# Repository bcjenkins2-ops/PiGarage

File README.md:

# PiGarage

Open-source Raspberry Pi power management and audio HAT for automotive head-unit use.

## Features

- **5V 5A Buck Converter** (TPS54560BQDDARQ1) — 7-16V input, Pi 5 compatible
- **I2S DAC** (PCM5122PWR) — 112dB SNR, noise-free audio output to external amplifier
- **ADC** (ADS1115) — 16-bit, for steering wheel resistor ladder controls
- **4-Channel Optoisolated 12V Sensing** — ACC, REV, ILL, AUX via LTV-847S
- **Safe Shutdown** — ACC-triggered power latch with GPIO hold (BCM25), crank ride-through
- **Battery Protection** — UVLO hard cutoff at 12.08V via TL431A comparator
- **Compatible** — Raspberry Pi 3, 4, and 5

## Board

| Parameter | Value |
|-----------|-------|
| Input Voltage | 7-16V (automotive 12V) |
| Output Voltage | 5.0V |
| Output Current | 5A continuous |
| DAC SNR | 112dB |
| DAC Interface | I2S |
| ADC Resolution | 16-bit, 4-channel |
| Sense Inputs | 4ch optoisolated |
| Board Format | Raspberry Pi HAT (65mm x 56.5mm) |

## Directory Layout

```
PiGarage/
├── Hardware/           KiCad 10 schematic, PCB, and custom libraries
├── Production/         Gerbers, drill files, pick-and-place
├── BOM/                Bill of Materials and design notes
├── Images/             Board renders and schematic exports
├── Software/           Power latch daemon and systemd service
└── Docs/               Ordering and assembly guide
```

## Getting Started

See [Docs/ordering-guide.md](Docs/ordering-guide.md) for full instructions on ordering from JLCPCB and assembling the board.

## License

Hardware: [CERN-OHL-S-2.0](https://ohwr.org/cern_ohl_s_v2.txt) — Software: MIT

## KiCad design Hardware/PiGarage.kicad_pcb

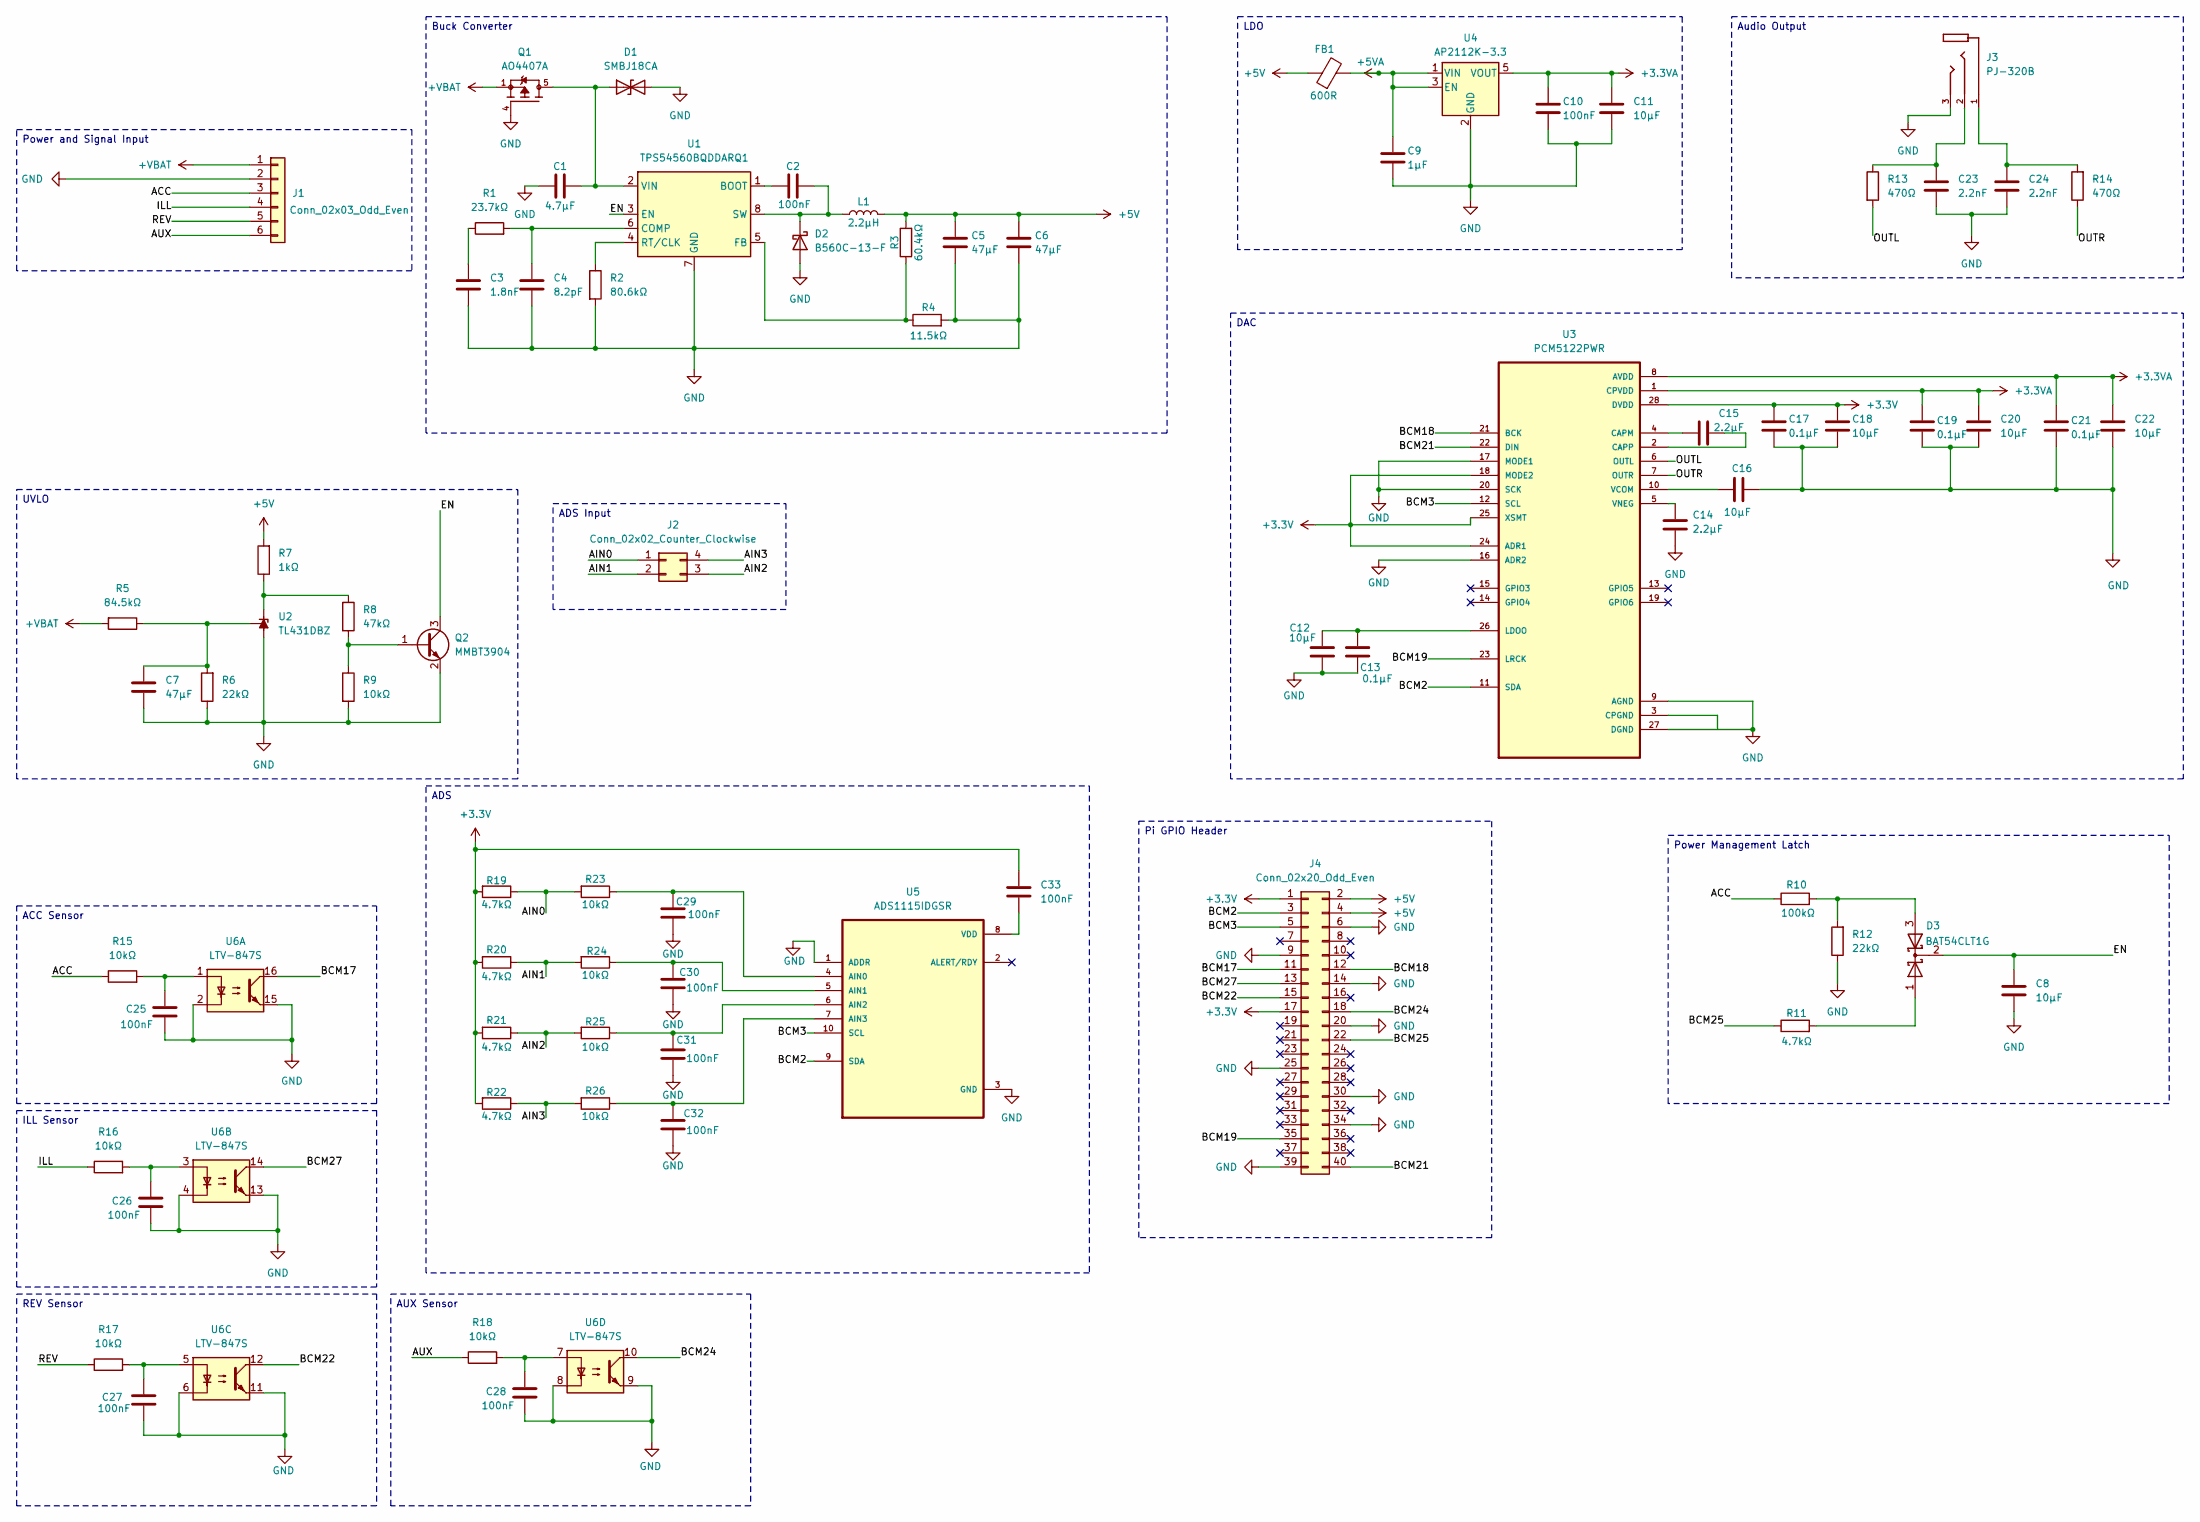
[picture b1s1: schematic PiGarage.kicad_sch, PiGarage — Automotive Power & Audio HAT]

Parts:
C1: 4.7µF; C_1206_3216Metric
C2, C10, C25, C26, C27, C28, C29, C30, C31, C32, C33: 100nF; C_0603_1608Metric
C3: 1.8nF; C_0603_1608Metric
C4: 8.2pF; C_0603_1608Metric
C5, C6, C7: 47µF; C_1206_3216Metric
C8, C11, C12, C16, C18, C20, C22: 10µF; C_0603_1608Metric
C9: 1µF; C_0603_1608Metric
C13, C17, C19, C21: 0.1µF; C_0603_1608Metric
C14, C15: 2.2µF; C_0603_1608Metric
C23, C24: 2.2nF; C_0603_1608Metric
D1: SMBJ18CA; D_SMC
D2: B560C-13-F; SMC_L7.1-W6.2-LS8.1-RD
D3: BAT54CLT1G; SOT-23
FB1: 600R; L_0603_1608Metric
J1: Conn_02x03_Odd_Even; Molex_Mini-Fit_Jr_5566-06A_2x03_P4.20mm_Vertical
J2: Conn_02x02_Counter_Clockwise; Molex_Mini-Fit_Jr_5566-04A_2x02_P4.20mm_Vertical
J3: PJ-320B; BOOMELE_PJ-320B; MPN PJ-320B
J4: Conn_02x20_Odd_Even; PinSocket_2x20_P2.54mm_Vertical
L1: 2.2µH; IND-SMD_L7.0-W6.6
Q1: AO4407A; SOIC127P600X175-8N; PARTREV I
Q2: MMBT3904; TSOT-23
R1: 23.7kΩ; R_0603_1608Metric
R2: 80.6kΩ; R_0603_1608Metric
R3: 60.4kΩ; R_0603_1608Metric
R4: 11.5kΩ; R_0603_1608Metric
R5: 84.5kΩ; R_0603_1608Metric
R6, R12: 22kΩ; R_0603_1608Metric
R7: 1kΩ; R_0603_1608Metric
R8: 47kΩ; R_0603_1608Metric
R9, R15, R16, R17, R18, R23, R24, R25, R26: 10kΩ; R_0603_1608Metric
R10: 100kΩ; R_0603_1608Metric
R11, R19, R20, R21, R22: 4.7kΩ; R_0603_1608Metric
R13, R14: 470Ω; R_0603_1608Metric
U1: TPS54560BQDDARQ1; Texas_R-PDSO-G8_EP2.95x4.9mm_Mask2.4x3.1mm_ThermalVias
U2: TL431DBZ; SOT-23
U3: PCM5122PWR; TSSOP-28_4.4x9.7mm_P0.65mm
U4: AP2112K-3.3; SOT-23-5
U5: ADS1115IDGSR; SOP50P490X110-10N
U6: LTV-847S; SMDIP-16_W9.53mm

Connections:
+3.3V: C17.1, C18.2, C33.1, J4.1, J4.17, R19.2, R20.2, R21.2, R22.2, U3.18 (MODE2), U3.24 (ADR1), U3.25 (XSMT), U3.28 (DVDD)
+3.3VA: C10.2, C11.2, C19.1, C20.2, C21.1, C22.2, U3.1 (CPVDD), U3.8 (AVDD), U4.5 (VOUT)
+5V: C5.1, C6.1, FB1.1, J4.2, J4.4, L1.2, R3.2, R7.2
+5VA: C9.1, FB1.2, U4.1 (VIN), U4.3 (EN)
/ACC: J1.3, R10.1, R15.1
/AIN0: J2.1, R19.1, R23.2
/AIN1: J2.2, R20.1, R24.2
/AIN2: J2.3, R21.1, R25.2
/AIN3: J2.4, R22.1, R26.2
/AUX: J1.6, R18.1
/BCM2: J4.3, U3.11 (SDA), U5.9 (SDA)
/BCM3: J4.5, U3.12 (SCL), U5.10 (SCL)
/BCM17: J4.11, U6.16
/BCM18: J4.12, U3.21 (BCK)
/BCM19: J4.35, U3.23 (LRCK)
/BCM21: J4.40, U3.22 (DIN)
/BCM22: J4.15, U6.12
/BCM24: J4.18, U6.10
/BCM25: J4.22, R11.1
/BCM27: J4.13, U6.14
/EN: C8.1, D3.2 (K), Q2.3 (C), U1.3 (EN)
/ILL: J1.4, R16.1
/OUTL: R13.2, U3.6 (OUTL)
/OUTR: R14.1, U3.7 (OUTR)
/REV: J1.5, R17.1
GND: C1.2, C3.2, C4.2, C5.2, C6.2, C7.1, C8.2, C9.2, C10.1, C11.1, C12.1, C13.1, C14.2, C16.1, C17.2, C18.1, C19.2, C20.1, C21.2, C22.1, C23.1, C24.2, C25.2, C26.2, C27.2, C28.2, C29.1, C30.2, C31.2, C32.2, D1.2 (A2), D2.2 (A), J1.2, J3.3, J4.6, J4.9, J4.14, J4.20, J4.25, J4.30, J4.34, J4.39, Q1.4, Q2.2 (E), R2.2, R4.2, R6.1, R9.2, R12.1, U1.7 (GND), U1.9 (GND), U2.3 (A), U3.9 (AGND), U3.16 (ADR2), U3.17 (MODE1), U3.20 (SCK), U3.27 (DGND), U4.2 (GND), U5.1 (ADDR), U5.3 (GND), U6.2, U6.4, U6.6, U6.8, U6.9, U6.11, U6.13, U6.15
unnamed: C3.1, R1.1
unnamed: C23.2, J3.2, R13.1
unnamed: C24.1, J3.1, R14.2
unnamed: C25.1, R15.2, U6.1
unnamed: C26.1, R16.2, U6.3
unnamed: C27.1, R17.2, U6.5
unnamed: C28.1, R18.2, U6.7
unnamed: C2.2, D2.1 (K), L1.1, U1.8 (SW)
unnamed: D3.1 (A), R11.2
unnamed: D3.3 (A), R10.2, R12.2
unnamed: Q2.1 (B), R8.2, R9.1
unnamed: C2.1, U1.1 (BOOT)
unnamed: C4.1, R1.2, U1.6 (COMP)
unnamed: R3.1, R4.1, U1.5 (FB)
unnamed: R2.1, U1.4 (RT/CLK)
unnamed: R7.1, R8.1, U2.1 (K)
unnamed: C7.2, R5.1, R6.2, U2.2 (REF)
unnamed: C15.2, U3.4 (CAPM)
unnamed: C15.1, U3.2 (CAPP)
unnamed: C12.2, C13.2, U3.26 (LDOO)
unnamed: C16.2, U3.10 (VCOM)
unnamed: C14.1, U3.5 (VNEG)
unnamed: C29.2, R23.1, U5.4 (AIN0)
unnamed: C30.1, R24.1, U5.5 (AIN1)
unnamed: C31.1, R25.1, U5.6 (AIN2)
unnamed: C32.1, R26.1, U5.7 (AIN3)
unnamed: C33.2, U5.8 (VDD)

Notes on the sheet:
Power Management Latch
Buck Converter
AUX Sensor
REV Sensor
DAC
LDO
ILL Sensor
ADS
ADS Input
Power and Signal Input
ACC Sensor
Pi GPIO Header
UVLO
Audio Output

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
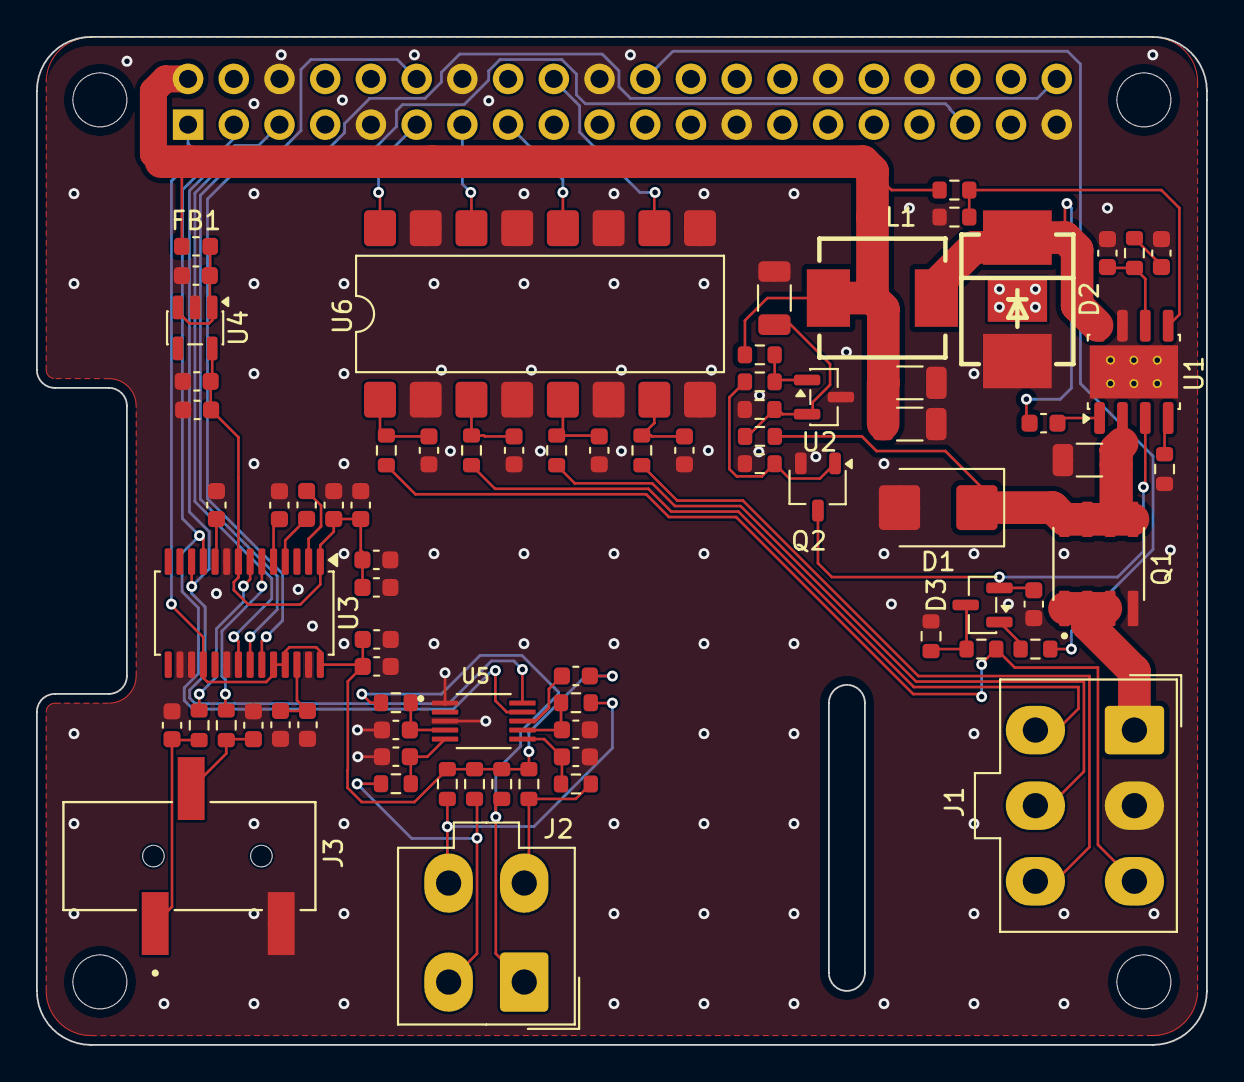
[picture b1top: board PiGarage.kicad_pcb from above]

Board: 2 copper layers, 65.0 x 56.0 mm, 76 parts (1 on the bottom side), 55 nets.

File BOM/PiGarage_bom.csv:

Reference,Qty,Value,Footprint,MPN,Manufacturer,LCSC,LC_Stock,Chosen_Distributor,Datasheet,Validated,DNP,Notes
C1,1,4.7µF,1206,,,,,,,,,
C3,1,1.8nF,0603,,,,,,,,,
C4,1,8.2pF,0603,,,,,,,,,
"C5,C6,C7",3,47µF,1206,,,,,,,,,
C9,1,1µF,0603,,,,,,,,,
"C11,C8,C22,C12,C18,C20,C16",7,10µF,0603,,,,,,,,,
"C15,C14",2,2.2µF,0603,,,,,,,,,
"C21,C13,C17,C19",4,0.1µF,0603,CC0603KRX7R9BB104,Yageo,C14663,,,,,,
"C23,C24",2,2.2nF,0603,,,,,,,,,
"C32,C2,C25,C31,C27,C33,C28,C10,C30,C26,C29",11,100nF,0603,,,,,,,,,
D1,1,SMBJ18CA,SMB,,,,,,,,,
D2,1,B560C-13-F,SMC_L7.1-W6.2-LS8.1-RD,,,,,,,,,
D3,1,BAT54CLT1G,SOT-23,,,,,,,,,
FB1,1,600R,0603,,,,,,,,,
J1,1,Conn_02x03_Odd_Even,Molex_Mini-Fit_Jr_5566-06A_2x03_P4.20mm_Vertical,,,,,,,,,
J2,1,Conn_02x02_Counter_Clockwise,Molex_Mini-Fit_Jr_5566-04A_2x02_P4.20mm_Vertical,,,,,,,,,
J3,1,PJ-320B,BOOMELE_PJ-320B,PJ-320B,Luoyang Dishang electronics,,,,,,,
J4,1,Conn_02x20_Odd_Even,PinSocket_2x20_P2.54mm_Vertical,,,,,,,,,
L1,1,2.2µH,IND-SMD_L7.0-W6.6,,,,,,,,,
Q1,1,AO4407A,SOIC127P600X175-8N,,,,,,,,,
Q2,1,MMBT3904,TSOT-23,,,,,,https://www.onsemi.com/pdf/datasheet/pzt3904-d.pdf,,,
R1,1,23.7kΩ,0603,,,,,,,,,
R2,1,80.6kΩ,0603,,,,,,,,,
R3,1,60.4kΩ,0603,,,,,,,,,
R4,1,11.5kΩ,0603,,,,,,,,,
R5,1,84.5kΩ,0603,0603WAF8452T5E,UNI-ROYAL(Uniroyal Elec),C23118,,,,,,
"R6,R12",2,22kΩ,0603,0603WAF2202T5E,UNI-ROYAL(Uniroyal Elec),C31850,,,,,,
R7,1,1kΩ,0603,0603WAF1001T5E,UNI-ROYAL(Uniroyal Elec),C21190,,,,,,
R8,1,47kΩ,0603,0603WAF4702T5E,UNI-ROYAL(Uniroyal Elec),C25819,,,,,,
R10,1,100kΩ,0603,0603WAF1003T5E,UNI-ROYAL(Uniroyal Elec),C25803,,,,,,
"R13,R14",2,470Ω,0603,0603WAF4700T5E,UNI-ROYAL(Uniroyal Elec),C23179,,,,,,
"R18,R15,R16,R23,R9,R17,R26,R24,R25",9,10kΩ,0603,0603WAF1002T5E,UNI-ROYAL(Uniroyal Elec),C25804,,,,,,
"R20,R19,R22,R11,R21",5,4.7kΩ,0603,0603WAF4701T5E,UNI-ROYAL(Uniroyal Elec),C23162,,,,,,
U1,1,TPS54560BQDDARQ1,Texas_R-PDSO-G8_EP2.95x4.9mm_Mask2.4x3.1mm_ThermalVias,,,,,,https://www.ti.com/lit/ds/symlink/tps54560b.pdf,,,
U2,1,TL431DBZ,SOT-23,,,,,,http://www.ti.com/lit/ds/symlink/tl431.pdf,,,
U3,1,PCM5122PWR,TSSOP-28_4.4x9.7mm_P0.65mm,,,,,,,,,
U4,1,AP2112K-3.3,SOT-23-5,,,,,,https://www.diodes.com/assets/Datasheets/AP2112.pdf,,,
U5,1,ADS1115IDGSR,SOP50P490X110-10N,,,,,,,,,
U6,1,LTV-847S,SMDIP-16_W9.53mm,,,,,,http://www.us.liteon.com/downloads/LTV-817-827-847.PDF,,,

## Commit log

2026-03-20 Initial commit — PiGarage v0.1
    Automotive 12V→5V power management and audio HAT for Raspberry Pi 3/4/5.
    KiCad 9 hardware design, production files, BOM, and power latch daemon.
2026-03-31 v0.2
    - Buck converter redesigned with TI WEBENCH (7-16V in, 5V/5A, 1.1MHz fsw)
    - New inductor: FXL0630-2R2-M (2.2µH, 10A Isat, 15mΩ DCR)
    - New catch diode: B560C-13-F (SMC package for better thermals)
    - Added AO4407A P-FET reverse polarity protection
    - Replaced 4× LTV-817S with 1× LTV-847S quad optocoupler
    - Switched ADS1115 back to VSSOP (IDGSR) from QFN
2026-04-03 Add thermal pad to D2 and remap GPIO sense pins
    - Added exposed copper thermal pad (GND, pad 3) with 4 thermal vias to
    D2 (B560C catch diode) footprint for improved heat dissipation at 5A
    - Remapped optoisolator GPIO assignments for cleaner PCB trace routing:
    BCM17 = ACC, BCM22 = REV, BCM27 = ILL, BCM24 = AUX
    - Updated power_latch.py PIN_ACC 27 → 17 to match new assignment
    - Updated design-notes and GPIO allocation table
2026-04-17 Fix D1 footprint: D_SMC (DO-214AB) → D_SMB (DO-214AA)
    SMBJ18CA ships in SMB (DO-214AA) package; the SMC footprint had
    ~60% larger pads and courtyard, causing JLCPCB preview mismatch.
    Updated pad positions (±3.4 → ±2.15 mm), pad size (3.3×2.5 →
    2.5×2.3 mm), courtyard, silkscreen, fab outline, and 3D model to
    match KiCad Diode_SMD:D_SMB. Re-routing of D1 connections required
    in KiCad after this change.
2026-04-17 Re-route D1 traces and refresh Gerbers after SMB footprint fix
    Updated D1 pad connections after pad positions shifted from ±3.4 mm
    to ±2.15 mm. Regenerated all Gerbers and drill files.
2026-04-17 Update front board image
2026-04-24 Update BOM and design notes: swap 0402 passives to 0603
    All affected resistors and decoupling caps updated to 0603 footprint
    equivalents to support hand soldering. LCSC part numbers, MPNs, and
    specs updated throughout design-notes.txt. Schematic symbol properties
    updated with new 0603 LCSC numbers. BOM tracking CSV added.

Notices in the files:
Hardware/PiGarage.kicad_pcb:
License: CERN-OHL-S-2.0
